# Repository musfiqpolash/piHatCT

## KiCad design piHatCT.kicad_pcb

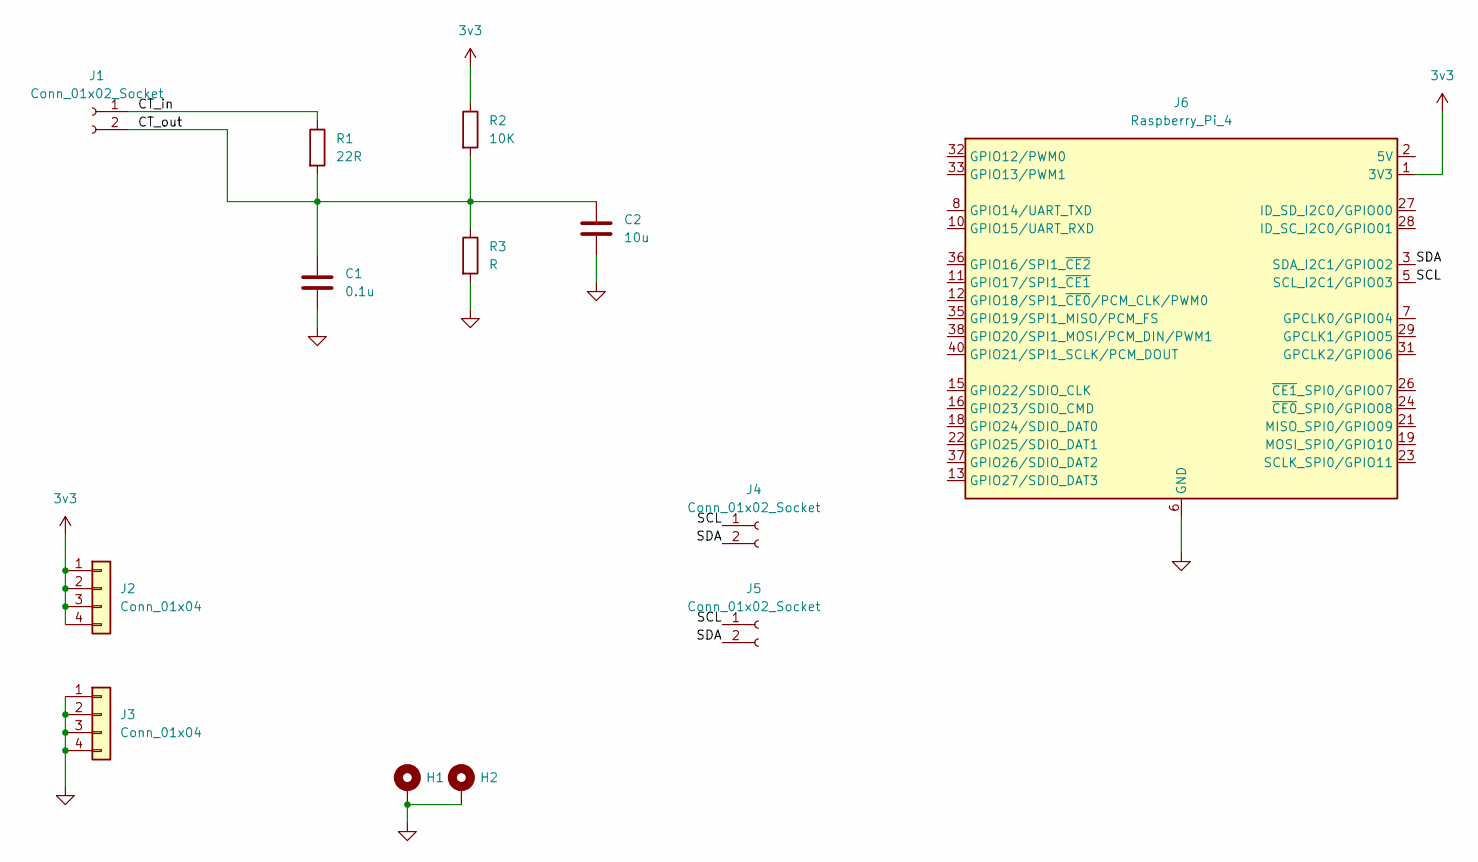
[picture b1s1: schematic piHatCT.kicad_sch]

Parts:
C1: 0.1u; C_0805_2012Metric_Pad1.18x1.45mm_HandSolder
C2: 10u; C_0805_2012Metric_Pad1.18x1.45mm_HandSolder
H1, H2: MountingHole_Pad; MountingHole_2.5mm_Pad_Via
J1, J4, J5: Conn_01x02_Socket; PhoenixContact_MCV_1,5_2-G-3.5_1x02_P3.50mm_Vertical
J2, J3: Conn_01x04; PhoenixContact_MCV_1,5_4-G-3.5_1x04_P3.50mm_Vertical
J6: Raspberry_Pi_4; PinHeader_2x20_P2.54mm_Vertical
R1: 22R; R_0805_2012Metric_Pad1.20x1.40mm_HandSolder
R2: 10K; R_0805_2012Metric_Pad1.20x1.40mm_HandSolder
R3: R; R_0805_2012Metric_Pad1.20x1.40mm_HandSolder

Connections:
3v3: J2.1, J2.2, J2.3, J2.4, J6.1 (3V3), J6.17 (3V3), R2.1
/CT_in: J1.1, R1.1
/CT_out: C1.1, C2.1, J1.2, R1.2, R2.2, R3.1
/SCL: J4.1, J5.1, J6.5 (SCL_I2C1/GPIO03)
/SDA: J4.2, J5.2, J6.3 (SDA_I2C1/GPIO02)
GND: C1.2, C2.2, H1.1, H2.1, J3.1, J3.2, J3.3, J3.4, J6.6 (GND), J6.9 (GND), J6.14 (GND), J6.20 (GND), J6.25 (GND), J6.30 (GND), J6.34 (GND), J6.39 (GND), R3.2
unnamed: J6.2 (5V), J6.4 (5V)

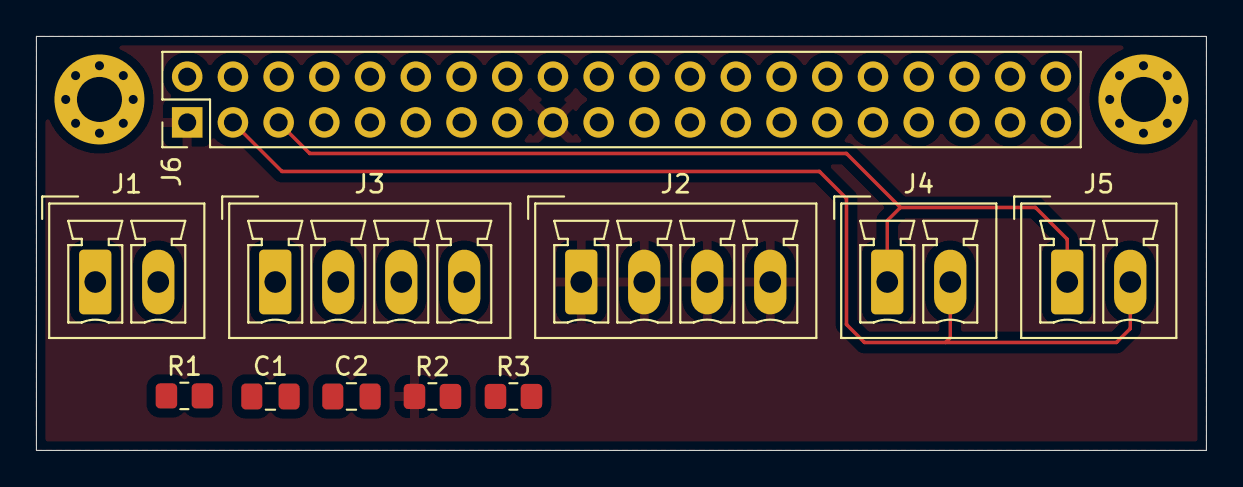
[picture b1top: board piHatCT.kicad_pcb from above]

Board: 2 copper layers, 65.0 x 23.0 mm, 13 parts (0 on the bottom side), 7 nets.

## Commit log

2025-05-04 files added
